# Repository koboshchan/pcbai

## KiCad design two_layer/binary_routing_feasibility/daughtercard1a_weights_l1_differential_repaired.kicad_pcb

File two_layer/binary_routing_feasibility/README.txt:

These four routed binary-model trials are engineering feasibility snapshots only.
They are NOT final grayscale boards and must NOT be fabricated.

DC1a and DC1c have strict zero DRC errors and zero unconnected items.
DC1b and DC1d each have three copper-edge routing errors, zero unconnected items.
Library-footprint warnings remain. No Gerbers or assembly files are released.

Model source was binary trained_circuit.json before approved PWM+RC grayscale
retraining. Final grayscale training and source10050ohm coupled input loading
will change resistor values and connections, requiring regenerated CAD/routers.
Straddle solder-pad tips recessed0.5mm preserve connectorposition and pinpitch;
actual purchased header pinreach still needs mechanical qualification.

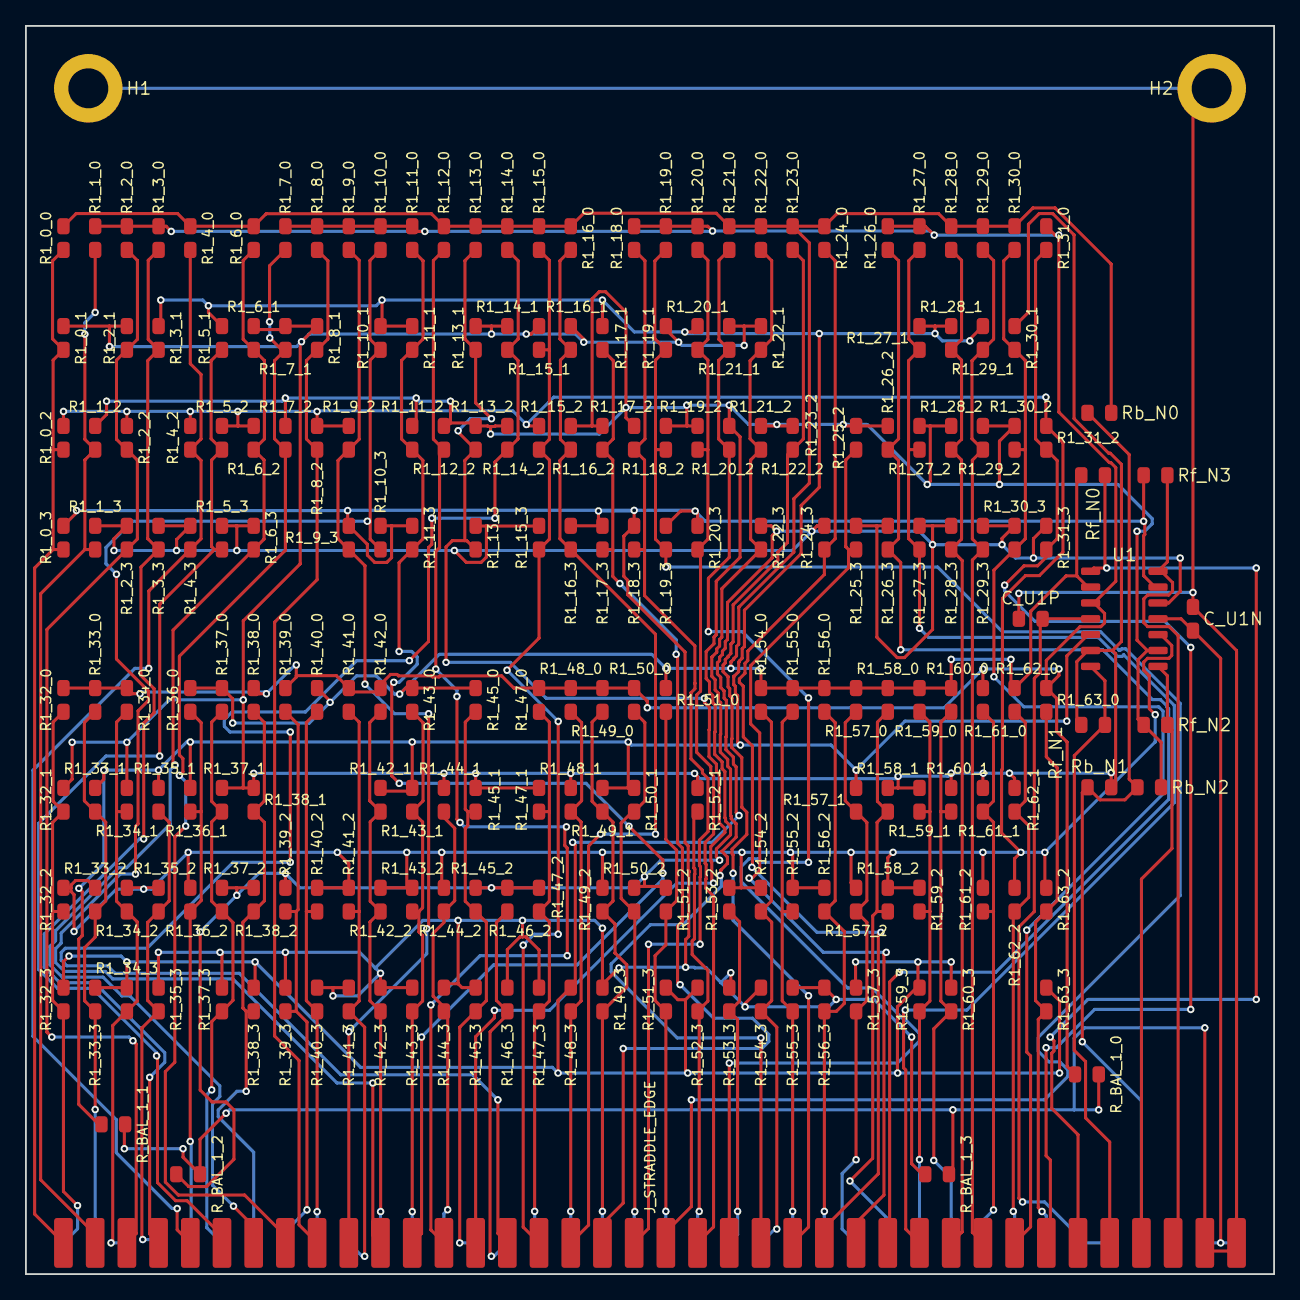
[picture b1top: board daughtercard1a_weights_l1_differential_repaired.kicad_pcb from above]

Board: 2 copper layers, 100.0 x 100.0 mm, 228 parts (0 on the bottom side), 80 nets.

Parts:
C_U1N, C_U1P: 0.1uF; C_0805_2012Metric
H1, H2: MountingHole; MountingHole_3.2mm_M3_Pad
J_STRADDLE_EDGE: PinHeader_2x38_Straddle; PinHeader_2x38_Straddle_P2.54mm
R1_0_0: 36k; R_0805_2012Metric
R1_0_1, R1_7_1, R1_14_2, R1_29_1, R1_31_0, R1_51_3, R1_59_2: 750k; R_0805_2012Metric
R1_0_2, R1_2_2, R1_8_1, R1_21_2, R1_59_0, R1_62_0: 200k; R_0805_2012Metric
R1_0_3, R1_2_3, R1_56_0, R1_62_2: 75k; R_0805_2012Metric
R1_1_0, R1_2_0, R1_8_2, R1_15_0, R1_24_0, R1_25_3, R1_27_0, R1_55_3, R1_59_3: 180k; R_0805_2012Metric
R1_1_2, R1_6_0, R1_21_1, R1_26_0, R1_26_2, R1_35_2, R1_37_1, R1_57_0: 360k; R_0805_2012Metric
R1_1_3, R1_4_3, R1_28_1, R1_31_3, R1_39_0: 91k; R_0805_2012Metric
R1_2_1, R1_11_3, R1_14_0, R1_28_0, R1_29_2, R1_33_0, R1_35_3, R1_38_1, R1_40_0, R1_46_3, R1_49_3, R1_52_3, R1_62_1: 470k; R_0805_2012Metric
R1_3_0, R1_19_0, R1_20_1, R1_22_0, R1_22_1, R1_39_2, R1_41_3, R1_42_2, R1_59_1: 270k; R_0805_2012Metric
R1_3_1, R1_6_1, R1_11_2, R1_34_1, R1_36_1, R1_37_0, R1_38_0, R1_38_2, R1_48_1, R1_53_2, R1_53_3, R1_63_0: 820k; R_0805_2012Metric
R1_3_3, R1_5_2, R1_6_3, R1_48_3: 100k; R_0805_2012Metric
R1_4_0, R1_8_0, R1_23_0, R1_32_0, R1_33_3, R1_56_3, R1_58_1: 240k; R_0805_2012Metric
R1_4_2, R1_9_2, R1_9_3, R1_14_1, R1_18_2, R1_21_0, R1_27_3, R1_37_2, R1_41_0, R1_47_3, R1_58_2: 430k; R_0805_2012Metric
R1_5_1, R1_17_1, R1_43_0, R1_49_0, R1_50_0: 1.6M; R_0805_2012Metric
R1_5_3, R1_57_2: 120k; R_0805_2012Metric
R1_6_2, R1_23_2, R1_55_0: 110k; R_0805_2012Metric
R1_7_0, R1_12_0, R1_27_2, R1_32_1, R1_43_1, R1_54_0, R1_55_2: 510k; R_0805_2012Metric
R1_7_2, R1_15_1, R1_19_2, R1_22_3, R1_25_2, R1_34_0, R1_34_2, R1_36_0, R1_44_2, R1_47_1: 560k; R_0805_2012Metric
R1_9_0, R1_13_0, R1_27_1, R1_29_0, R1_36_2, R1_54_2: 390k; R_0805_2012Metric
R1_10_0, R1_10_3, R1_16_1, R1_44_1, R1_45_1, R1_58_0, R1_60_0: 330k; R_0805_2012Metric
R1_10_1, R1_41_2, R1_42_1, R1_43_3, R1_51_2: 1.3M; R_0805_2012Metric
R1_11_0, R1_12_2, R1_30_0, R1_33_1, R1_61_0: 1.8M; R_0805_2012Metric
R1_11_1, R1_16_2, R1_19_1, R1_28_2, R1_38_3, R1_47_2: 1.5M; R_0805_2012Metric
R1_13_1, R1_20_2, R1_30_1, R1_37_3, R1_45_0, R1_45_2, R1_48_0, R1_49_2: 910k; R_0805_2012Metric
R1_13_2, R1_16_0, R1_17_2, R1_20_0, R1_33_2, R1_34_3, R1_42_3, R1_49_1, R1_52_1: 680k; R_0805_2012Metric
R1_13_3, R1_44_3, R1_45_3, R1_60_1, R1_61_1: 1M; R_0805_2012Metric
R1_15_2, R1_17_3, R1_39_3: 150k; R_0805_2012Metric
R1_15_3: 160k; R_0805_2012Metric
R1_16_3, R1_31_2, R1_61_2: 82k; R_0805_2012Metric
R1_18_0: 3.9M; R_0805_2012Metric
R1_18_3, R1_19_3, R1_35_1, R1_40_2, R1_57_3, R1_60_3: 300k; R_0805_2012Metric
R1_20_3: 3.3M; R_0805_2012Metric
R1_22_2, R1_32_2: 130k; R_0805_2012Metric
R1_24_3, R1_63_3: 51k; R_0805_2012Metric
R1_26_3, R1_43_2, R1_56_2: 220k; R_0805_2012Metric
R1_28_3, R1_29_3, R1_50_1: 1.2M; R_0805_2012Metric
R1_30_2, R1_42_0, R1_57_1: 620k; R_0805_2012Metric
R1_30_3: 2M; R_0805_2012Metric
R1_32_3: 24k; R_0805_2012Metric
R1_40_3, R1_47_0: 68k; R_0805_2012Metric
R1_46_2: 1.1M; R_0805_2012Metric
R1_50_2: 4.3M; R_0805_2012Metric
R1_51_0: 2.2M; R_0805_2012Metric
R1_54_3: 3.6M; R_0805_2012Metric
R1_63_2: 43k; R_0805_2012Metric
R_BAL_1_0: 21.5k; R_0805_2012Metric
R_BAL_1_1: 28.7k; R_0805_2012Metric
R_BAL_1_2: 11.5k; R_0805_2012Metric
R_BAL_1_3: 9.53k; R_0805_2012Metric
Rb_N0: 470k; R_0805_2012Metric
Rb_N1: 910k; R_0805_2012Metric
Rb_N2: 270k; R_0805_2012Metric
Rf_N0, Rf_N1, Rf_N2, Rf_N3: 100k; R_0805_2012Metric
U1: TL074; SOIC-14_3.9x8.7mm_P1.27mm

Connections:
+5V_REF: J_STRADDLE_EDGE.B35, Rb_N0.1, Rb_N1.1, Rb_N2.1
+15V: C_U1P.2, J_STRADDLE_EDGE.B33, J_STRADDLE_EDGE.B34, U1.4
-15V: C_U1N.1, J_STRADDLE_EDGE.B37, J_STRADDLE_EDGE.B38, U1.11
GND: C_U1N.2, C_U1P.1, H1.1, H2.1, J_STRADDLE_EDGE.A37, J_STRADDLE_EDGE.A38, R_BAL_1_0.2, R_BAL_1_1.2, R_BAL_1_2.2, R_BAL_1_3.2
INV_N0: R1_0_0.2, R1_4_0.2, R1_6_0.2, R1_12_0.2, R1_13_0.2, R1_14_0.2, R1_15_0.2, R1_16_0.2, R1_21_0.2, R1_22_0.2, R1_23_0.2, R1_24_0.2, R1_28_0.2, R1_29_0.2, R1_30_0.2, R1_36_0.2, R1_37_0.2, R1_40_0.2, R1_43_0.2, R1_45_0.2, R1_51_0.2, R1_54_0.2, R1_55_0.2, R1_56_0.2, R1_57_0.2, R1_58_0.2, R1_59_0.2, R1_60_0.2, R1_62_0.2, Rb_N0.2, Rf_N0.1, U1.2
INV_N1: R1_0_1.2, R1_2_1.2, R1_6_1.2, R1_7_1.2, R1_8_1.2, R1_13_1.2, R1_14_1.2, R1_15_1.2, R1_16_1.2, R1_19_1.2, R1_21_1.2, R1_22_1.2, R1_30_1.2, R1_32_1.2, R1_34_1.2, R1_37_1.2, R1_38_1.2, R1_44_1.2, R1_45_1.2, R1_47_1.2, R1_48_1.2, R1_52_1.2, R1_58_1.2, R1_59_1.2, R1_60_1.2, R1_61_1.2, R1_62_1.2, Rb_N1.2, Rf_N1.1, U1.6
INV_N2: R1_1_2.2, R1_7_2.2, R1_11_2.2, R1_12_2.2, R1_13_2.2, R1_14_2.2, R1_16_2.2, R1_17_2.2, R1_18_2.2, R1_19_2.2, R1_20_2.2, R1_21_2.2, R1_22_2.2, R1_23_2.2, R1_25_2.2, R1_26_2.2, R1_27_2.2, R1_28_2.2, R1_29_2.2, R1_30_2.2, R1_37_2.2, R1_38_2.2, R1_39_2.2, R1_45_2.2, R1_46_2.2, R1_47_2.2, R1_50_2.2, R1_51_2.2, R_BAL_1_2.1, Rb_N2.2, Rf_N2.1, U1.9
INV_N3: R1_0_3.2, R1_9_3.2, R1_10_3.2, R1_11_3.2, R1_16_3.2, R1_17_3.2, R1_18_3.2, R1_19_3.2, R1_20_3.2, R1_35_3.2, R1_37_3.2, R1_39_3.2, R1_40_3.2, R1_41_3.2, R1_42_3.2, R1_43_3.2, R1_44_3.2, R1_45_3.2, R1_46_3.2, R1_47_3.2, R1_49_3.2, R1_53_3.2, R1_54_3.2, R1_55_3.2, R1_56_3.2, R_BAL_1_3.1, Rf_N3.1, U1.13
IN_0: J_STRADDLE_EDGE.A1, R1_0_0.1, R1_0_1.1, R1_0_2.1, R1_0_3.1
IN_1: J_STRADDLE_EDGE.A2, R1_1_0.1, R1_1_2.1, R1_1_3.1
IN_2: J_STRADDLE_EDGE.A3, R1_2_0.1, R1_2_1.1, R1_2_2.1, R1_2_3.1
IN_3: J_STRADDLE_EDGE.A4, R1_3_0.1, R1_3_1.1, R1_3_3.1
IN_4: J_STRADDLE_EDGE.A5, R1_4_0.1, R1_4_2.1, R1_4_3.1
IN_5: J_STRADDLE_EDGE.A6, R1_5_1.1, R1_5_2.1, R1_5_3.1
IN_6: J_STRADDLE_EDGE.A7, R1_6_0.1, R1_6_1.1, R1_6_2.1, R1_6_3.1
IN_7: J_STRADDLE_EDGE.A8, R1_7_0.1, R1_7_1.1, R1_7_2.1
IN_8: J_STRADDLE_EDGE.A9, R1_8_0.1, R1_8_1.1, R1_8_2.1
IN_9: J_STRADDLE_EDGE.A10, R1_9_0.1, R1_9_2.1, R1_9_3.1
IN_10: J_STRADDLE_EDGE.A11, R1_10_0.1, R1_10_1.1, R1_10_3.1
IN_11: J_STRADDLE_EDGE.A12, R1_11_0.1, R1_11_1.1, R1_11_2.1, R1_11_3.1
IN_12: J_STRADDLE_EDGE.A13, R1_12_0.1, R1_12_2.1
IN_13: J_STRADDLE_EDGE.A14, R1_13_0.1, R1_13_1.1, R1_13_2.1, R1_13_3.1
IN_14: J_STRADDLE_EDGE.A15, R1_14_0.1, R1_14_1.1, R1_14_2.1
IN_15: J_STRADDLE_EDGE.A16, R1_15_0.1, R1_15_1.1, R1_15_2.1, R1_15_3.1
IN_16: J_STRADDLE_EDGE.A17, R1_16_0.1, R1_16_1.1, R1_16_2.1, R1_16_3.1
IN_17: J_STRADDLE_EDGE.A18, R1_17_1.1, R1_17_2.1, R1_17_3.1
IN_18: J_STRADDLE_EDGE.A19, R1_18_0.1, R1_18_2.1, R1_18_3.1
IN_19: J_STRADDLE_EDGE.A20, R1_19_0.1, R1_19_1.1, R1_19_2.1, R1_19_3.1
IN_20: J_STRADDLE_EDGE.A21, R1_20_0.1, R1_20_1.1, R1_20_2.1, R1_20_3.1
IN_21: J_STRADDLE_EDGE.A22, R1_21_0.1, R1_21_1.1, R1_21_2.1
IN_22: J_STRADDLE_EDGE.A23, R1_22_0.1, R1_22_1.1, R1_22_2.1, R1_22_3.1
IN_23: J_STRADDLE_EDGE.A24, R1_23_0.1, R1_23_2.1
IN_24: J_STRADDLE_EDGE.A25, R1_24_0.1, R1_24_3.1
IN_25: J_STRADDLE_EDGE.A26, R1_25_2.1, R1_25_3.1
IN_26: J_STRADDLE_EDGE.A27, R1_26_0.1, R1_26_2.1, R1_26_3.1
IN_27: J_STRADDLE_EDGE.A28, R1_27_0.1, R1_27_1.1, R1_27_2.1, R1_27_3.1
IN_28: J_STRADDLE_EDGE.A29, R1_28_0.1, R1_28_1.1, R1_28_2.1, R1_28_3.1
IN_29: J_STRADDLE_EDGE.A30, R1_29_0.1, R1_29_1.1, R1_29_2.1, R1_29_3.1
IN_30: J_STRADDLE_EDGE.A31, R1_30_0.1, R1_30_1.1, R1_30_2.1, R1_30_3.1
IN_31: J_STRADDLE_EDGE.A32, R1_31_0.1, R1_31_2.1, R1_31_3.1
IN_32: J_STRADDLE_EDGE.B1, R1_32_0.1, R1_32_1.1, R1_32_2.1, R1_32_3.1
IN_33: J_STRADDLE_EDGE.B2, R1_33_0.1, R1_33_1.1, R1_33_2.1, R1_33_3.1
IN_34: J_STRADDLE_EDGE.B3, R1_34_0.1, R1_34_1.1, R1_34_2.1, R1_34_3.1
IN_35: J_STRADDLE_EDGE.B4, R1_35_1.1, R1_35_2.1, R1_35_3.1
IN_36: J_STRADDLE_EDGE.B5, R1_36_0.1, R1_36_1.1, R1_36_2.1
IN_37: J_STRADDLE_EDGE.B6, R1_37_0.1, R1_37_1.1, R1_37_2.1, R1_37_3.1
IN_38: J_STRADDLE_EDGE.B7, R1_38_0.1, R1_38_1.1, R1_38_2.1, R1_38_3.1
IN_39: J_STRADDLE_EDGE.B8, R1_39_0.1, R1_39_2.1, R1_39_3.1
IN_40: J_STRADDLE_EDGE.B9, R1_40_0.1, R1_40_2.1, R1_40_3.1
IN_41: J_STRADDLE_EDGE.B10, R1_41_0.1, R1_41_2.1, R1_41_3.1
IN_42: J_STRADDLE_EDGE.B11, R1_42_0.1, R1_42_1.1, R1_42_2.1, R1_42_3.1
IN_43: J_STRADDLE_EDGE.B12, R1_43_0.1, R1_43_1.1, R1_43_2.1, R1_43_3.1
IN_44: J_STRADDLE_EDGE.B13, R1_44_1.1, R1_44_2.1, R1_44_3.1
IN_45: J_STRADDLE_EDGE.B14, R1_45_0.1, R1_45_1.1, R1_45_2.1, R1_45_3.1
IN_46: J_STRADDLE_EDGE.B15, R1_46_2.1, R1_46_3.1
IN_47: J_STRADDLE_EDGE.B16, R1_47_0.1, R1_47_1.1, R1_47_2.1, R1_47_3.1
IN_48: J_STRADDLE_EDGE.B17, R1_48_0.1, R1_48_1.1, R1_48_3.1
IN_49: J_STRADDLE_EDGE.B18, R1_49_0.1, R1_49_1.1, R1_49_2.1, R1_49_3.1
IN_50: J_STRADDLE_EDGE.B19, R1_50_0.1, R1_50_1.1, R1_50_2.1
IN_51: J_STRADDLE_EDGE.B20, R1_51_0.1, R1_51_2.1, R1_51_3.1
IN_52: J_STRADDLE_EDGE.B21, R1_52_1.1, R1_52_3.1
IN_53: J_STRADDLE_EDGE.B22, R1_53_2.1, R1_53_3.1
IN_54: J_STRADDLE_EDGE.B23, R1_54_0.1, R1_54_2.1, R1_54_3.1
IN_55: J_STRADDLE_EDGE.B24, R1_55_0.1, R1_55_2.1, R1_55_3.1
IN_56: J_STRADDLE_EDGE.B25, R1_56_0.1, R1_56_2.1, R1_56_3.1
IN_57: J_STRADDLE_EDGE.B26, R1_57_0.1, R1_57_1.1, R1_57_2.1, R1_57_3.1
IN_58: J_STRADDLE_EDGE.B27, R1_58_0.1, R1_58_1.1, R1_58_2.1
IN_59: J_STRADDLE_EDGE.B28, R1_59_0.1, R1_59_1.1, R1_59_2.1, R1_59_3.1
IN_60: J_STRADDLE_EDGE.B29, R1_60_0.1, R1_60_1.1, R1_60_3.1
IN_61: J_STRADDLE_EDGE.B30, R1_61_0.1, R1_61_1.1, R1_61_2.1
IN_62: J_STRADDLE_EDGE.B31, R1_62_0.1, R1_62_1.1, R1_62_2.1
IN_63: J_STRADDLE_EDGE.B32, R1_63_0.1, R1_63_2.1, R1_63_3.1
POS_N0: R1_1_0.2, R1_2_0.2, R1_3_0.2, R1_7_0.2, R1_8_0.2, R1_9_0.2, R1_10_0.2, R1_11_0.2, R1_18_0.2, R1_19_0.2, R1_20_0.2, R1_26_0.2, R1_27_0.2, R1_31_0.2, R1_32_0.2, R1_33_0.2, R1_34_0.2, R1_38_0.2, R1_39_0.2, R1_41_0.2, R1_42_0.2, R1_47_0.2, R1_48_0.2, R1_49_0.2, R1_50_0.2, R1_61_0.2, R1_63_0.2, R_BAL_1_0.1, U1.3
POS_N1: R1_3_1.2, R1_5_1.2, R1_10_1.2, R1_11_1.2, R1_17_1.2, R1_20_1.2, R1_27_1.2, R1_28_1.2, R1_29_1.2, R1_33_1.2, R1_35_1.2, R1_36_1.2, R1_42_1.2, R1_43_1.2, R1_49_1.2, R1_50_1.2, R1_57_1.2, R_BAL_1_1.1, U1.5
POS_N2: R1_0_2.2, R1_2_2.2, R1_4_2.2, R1_5_2.2, R1_6_2.2, R1_8_2.2, R1_9_2.2, R1_15_2.2, R1_31_2.2, R1_32_2.2, R1_33_2.2, R1_34_2.2, R1_35_2.2, R1_36_2.2, R1_40_2.2, R1_41_2.2, R1_42_2.2, R1_43_2.2, R1_44_2.2, R1_49_2.2, R1_53_2.2, R1_54_2.2, R1_55_2.2, R1_56_2.2, R1_57_2.2, R1_58_2.2, R1_59_2.2, R1_61_2.2, R1_62_2.2, R1_63_2.2, U1.10
POS_N3: R1_1_3.2, R1_2_3.2, R1_3_3.2, R1_4_3.2, R1_5_3.2, R1_6_3.2, R1_13_3.2, R1_15_3.2, R1_22_3.2, R1_24_3.2, R1_25_3.2, R1_26_3.2, R1_27_3.2, R1_28_3.2, R1_29_3.2, R1_30_3.2, R1_31_3.2, R1_32_3.2, R1_33_3.2, R1_34_3.2, R1_38_3.2, R1_48_3.2, R1_51_3.2, R1_52_3.2, R1_57_3.2, R1_59_3.2, R1_60_3.2, R1_63_3.2, U1.12
V_SUM_0: J_STRADDLE_EDGE.A33, Rf_N0.2, U1.1
V_SUM_1: J_STRADDLE_EDGE.A34, Rf_N1.2, U1.7
V_SUM_2: J_STRADDLE_EDGE.A35, Rf_N2.2, U1.8
V_SUM_3: J_STRADDLE_EDGE.A36, Rf_N3.2, U1.14

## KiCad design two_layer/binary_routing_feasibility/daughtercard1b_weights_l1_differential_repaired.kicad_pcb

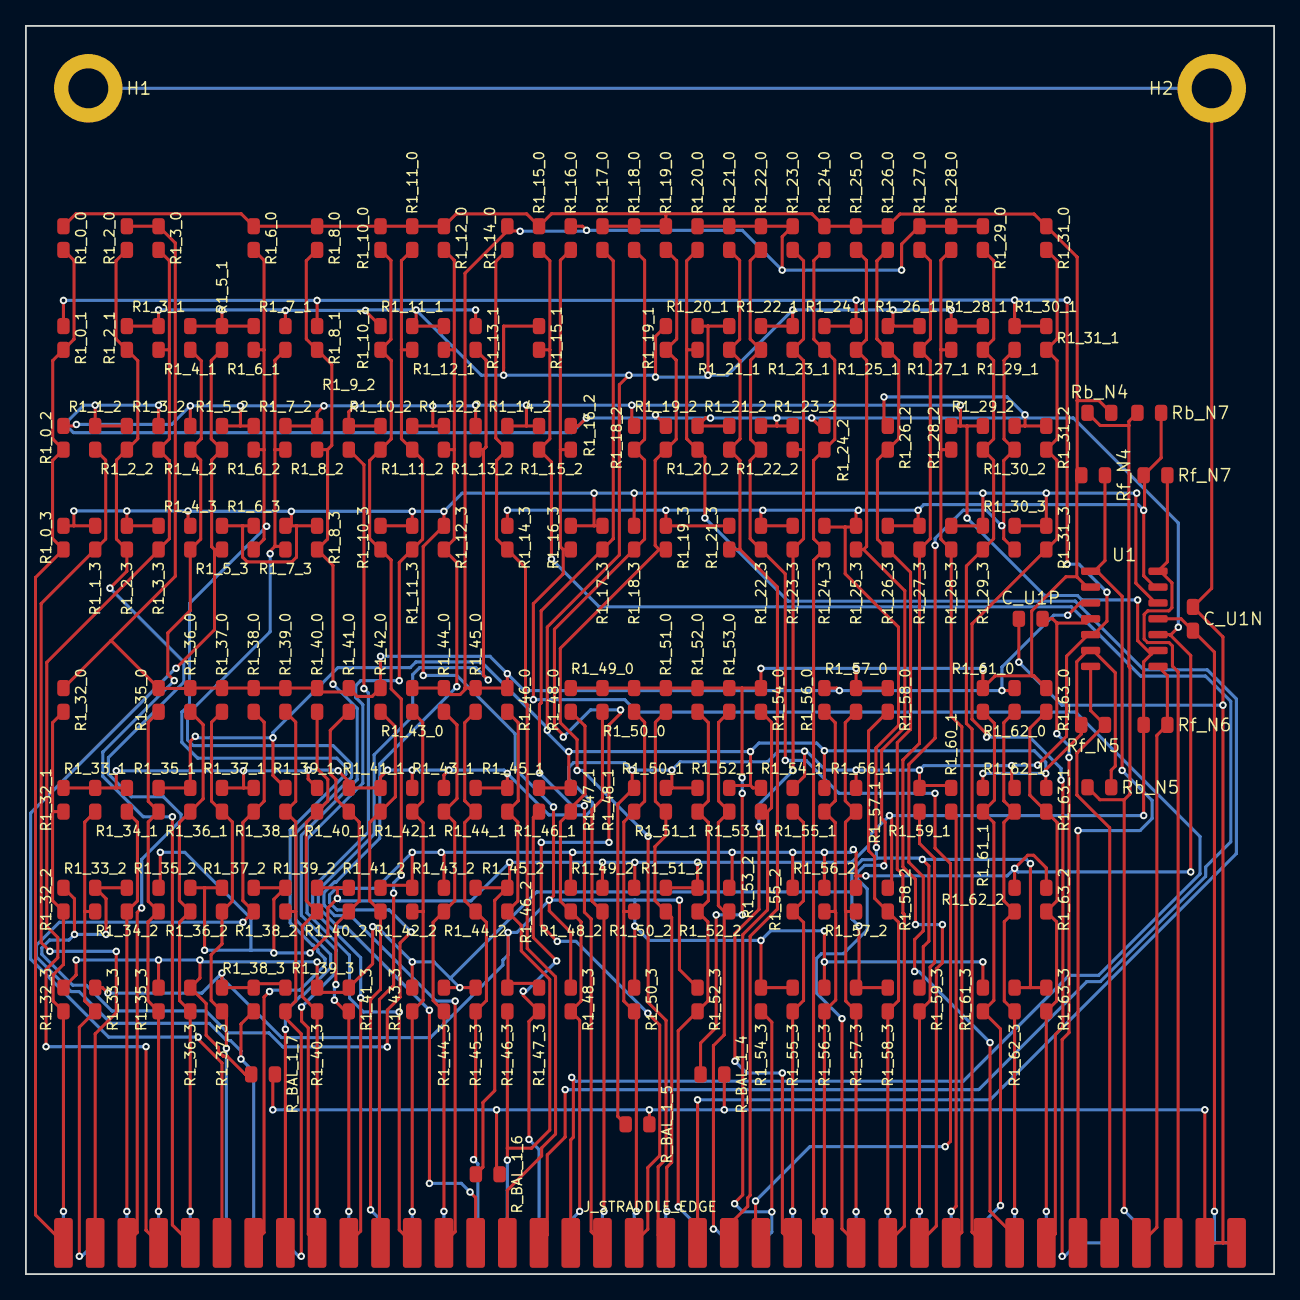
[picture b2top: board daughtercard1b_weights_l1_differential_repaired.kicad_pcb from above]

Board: 2 copper layers, 100.0 x 100.0 mm, 234 parts (0 on the bottom side), 80 nets.

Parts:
C_U1N, C_U1P: 0.1uF; C_0805_2012Metric
H1, H2: MountingHole; MountingHole_3.2mm_M3_Pad
J_STRADDLE_EDGE: PinHeader_2x38_Straddle; PinHeader_2x38_Straddle_P2.54mm
R1_0_0, R1_4_3, R1_16_2, R1_38_3, R1_55_3: 100k; R_0805_2012Metric
R1_0_1, R1_15_2, R1_56_1, R1_56_2: 56k; R_0805_2012Metric
R1_0_2, R1_3_2, R1_6_0, R1_10_1, R1_22_0, R1_28_0, R1_28_3, R1_35_0, R1_37_2, R1_38_2: 330k; R_0805_2012Metric
R1_0_3, R1_7_1, R1_32_0: 51k; R_0805_2012Metric
R1_1_2, R1_2_3, R1_20_0, R1_24_0, R1_27_0, R1_28_1, R1_55_1: 300k; R_0805_2012Metric
R1_1_3, R1_39_0, R1_62_2: 75k; R_0805_2012Metric
R1_2_0, R1_2_2, R1_3_1, R1_4_2, R1_11_0, R1_22_3, R1_43_0, R1_46_2, R1_52_0, R1_58_0, R1_61_3: 270k; R_0805_2012Metric
R1_2_1, R1_17_0, R1_21_1, R1_35_3, R1_43_3, R1_52_2, R1_62_3: 680k; R_0805_2012Metric
R1_3_0, R1_5_2, R1_16_0, R1_16_3, R1_31_0, R1_32_2, R1_39_2, R1_49_0, R1_56_0, R1_63_2: 150k; R_0805_2012Metric
R1_3_3, R1_27_1, R1_42_1, R1_47_1, R1_54_0, R1_55_2, R1_57_2, R1_62_1, R1_63_0: 220k; R_0805_2012Metric
R1_4_1, R1_12_0, R1_14_0, R1_14_3, R1_36_2, R1_41_3, R1_44_0, R1_50_1, R1_51_1: 620k; R_0805_2012Metric
R1_5_1, R1_9_2, R1_57_1: 560k; R_0805_2012Metric
R1_5_3, R1_32_1, R1_40_1, R1_47_3: 91k; R_0805_2012Metric
R1_6_1, R1_52_1: 1.3M; R_0805_2012Metric
R1_6_2, R1_7_2, R1_41_0: 82k; R_0805_2012Metric
R1_6_3: 68k; R_0805_2012Metric
R1_7_3, R1_23_1, R1_48_2: 120k; R_0805_2012Metric
R1_8_0, R1_15_0, R1_37_1, R1_44_2, R1_52_3: 2.4M; R_0805_2012Metric
R1_8_1, R1_20_2, R1_24_3, R1_32_3: 200k; R_0805_2012Metric
R1_8_2: 5.6M; R_0805_2012Metric
R1_8_3, R1_21_2, R1_22_2, R1_31_1: 110k; R_0805_2012Metric
R1_10_0, R1_24_2, R1_30_2, R1_48_0: 470k; R_0805_2012Metric
R1_10_2, R1_11_2, R1_18_2, R1_50_3: 1.5M; R_0805_2012Metric
R1_10_3, R1_12_3, R1_19_3, R1_21_3, R1_38_1, R1_49_2: 2M; R_0805_2012Metric
R1_11_1, R1_18_0, R1_25_0, R1_29_0, R1_33_1, R1_35_1, R1_61_0: 430k; R_0805_2012Metric
R1_11_3, R1_19_0, R1_42_2, R1_51_2, R1_60_1: 910k; R_0805_2012Metric
R1_12_1, R1_34_1, R1_34_2, R1_36_1, R1_37_3, R1_48_1, R1_53_1: 1.2M; R_0805_2012Metric
R1_12_2, R1_20_1, R1_22_1, R1_29_2, R1_45_1, R1_57_0, R1_59_1: 820k; R_0805_2012Metric
R1_13_1, R1_19_1, R1_29_1, R1_35_2: 1.8M; R_0805_2012Metric
R1_13_2, R1_33_2, R1_37_0, R1_43_1, R1_45_2, R1_51_0, R1_63_1: 390k; R_0805_2012Metric
R1_14_2, R1_38_0, R1_40_3, R1_46_3, R1_53_0: 180k; R_0805_2012Metric
R1_15_1, R1_41_1, R1_50_0, R1_54_3, R1_58_2: 240k; R_0805_2012Metric
R1_17_3: 3M; R_0805_2012Metric
R1_18_3, R1_46_1: 4.3M; R_0805_2012Metric
R1_19_2, R1_25_1, R1_46_0, R1_48_3, R1_50_2, R1_61_1: 1.1M; R_0805_2012Metric
R1_21_0, R1_28_2, R1_43_2, R1_44_3, R1_56_3: 510k; R_0805_2012Metric
R1_23_0, R1_24_1: 130k; R_0805_2012Metric
R1_23_2, R1_31_2, R1_31_3: 39k; R_0805_2012Metric
R1_23_3: 30k; R_0805_2012Metric
R1_25_3, R1_26_0, R1_33_3, R1_39_1, R1_44_1, R1_45_0: 750k; R_0805_2012Metric
R1_26_1, R1_45_3, R1_54_1: 1M; R_0805_2012Metric
R1_26_2, R1_26_3, R1_27_3, R1_41_2, R1_53_2, R1_57_3: 2.2M; R_0805_2012Metric
R1_29_3: 62k; R_0805_2012Metric
R1_30_1: 3.3M; R_0805_2012Metric
R1_30_3: 22k; R_0805_2012Metric
R1_36_0, R1_40_2: 360k; R_0805_2012Metric
R1_36_3: 2.7M; R_0805_2012Metric
R1_39_3: 27k; R_0805_2012Metric
R1_40_0: 43k; R_0805_2012Metric
R1_42_0, R1_62_0: 160k; R_0805_2012Metric
R1_58_3, R1_59_3: 1.6M; R_0805_2012Metric
R1_63_3: 47k; R_0805_2012Metric
R_BAL_1_4: 16.9k; R_0805_2012Metric
R_BAL_1_5: 80.6k; R_0805_2012Metric
R_BAL_1_6: 18.2k; R_0805_2012Metric
R_BAL_1_7: 5.62k; R_0805_2012Metric
Rb_N4: 330k; R_0805_2012Metric
Rb_N5: 240k; R_0805_2012Metric
Rb_N7: 360k; R_0805_2012Metric
Rf_N4, Rf_N5, Rf_N6, Rf_N7: 100k; R_0805_2012Metric
U1: TL074; SOIC-14_3.9x8.7mm_P1.27mm

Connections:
+5V_REF: J_STRADDLE_EDGE.B35, Rb_N4.1, Rb_N5.1, Rb_N7.1
+15V: C_U1P.2, J_STRADDLE_EDGE.B33, J_STRADDLE_EDGE.B34, U1.4
-15V: C_U1N.1, J_STRADDLE_EDGE.B37, J_STRADDLE_EDGE.B38, U1.11
GND: C_U1N.2, C_U1P.1, H1.1, H2.1, J_STRADDLE_EDGE.A37, J_STRADDLE_EDGE.A38, R_BAL_1_4.2, R_BAL_1_5.2, R_BAL_1_6.2, R_BAL_1_7.2
INV_N4: R1_0_0.2, R1_6_0.2, R1_8_0.2, R1_10_0.2, R1_11_0.2, R1_12_0.2, R1_15_0.2, R1_17_0.2, R1_18_0.2, R1_19_0.2, R1_24_0.2, R1_25_0.2, R1_26_0.2, R1_31_0.2, R1_48_0.2, R1_49_0.2, R1_50_0.2, R1_51_0.2, R1_52_0.2, R1_53_0.2, R1_54_0.2, R1_57_0.2, R1_58_0.2, R1_61_0.2, R1_63_0.2, R_BAL_1_4.1, Rb_N4.2, Rf_N4.1, U1.2
INV_N5: R1_2_1.2, R1_3_1.2, R1_4_1.2, R1_5_1.2, R1_6_1.2, R1_7_1.2, R1_10_1.2, R1_11_1.2, R1_12_1.2, R1_13_1.2, R1_15_1.2, R1_19_1.2, R1_20_1.2, R1_21_1.2, R1_22_1.2, R1_23_1.2, R1_26_1.2, R1_27_1.2, R1_28_1.2, R1_29_1.2, R1_35_1.2, R1_36_1.2, R1_39_1.2, R1_47_1.2, R1_48_1.2, R1_53_1.2, R1_54_1.2, R1_56_1.2, R1_61_1.2, R1_63_1.2, Rb_N5.2, Rf_N5.1, U1.6
INV_N6: R1_0_2.2, R1_4_2.2, R1_5_2.2, R1_6_2.2, R1_7_2.2, R1_8_2.2, R1_9_2.2, R1_10_2.2, R1_11_2.2, R1_12_2.2, R1_13_2.2, R1_14_2.2, R1_15_2.2, R1_18_2.2, R1_28_2.2, R1_29_2.2, R1_35_2.2, R1_36_2.2, R1_37_2.2, R1_38_2.2, R1_39_2.2, R1_40_2.2, R1_41_2.2, R1_45_2.2, R1_46_2.2, R1_49_2.2, R1_50_2.2, R1_51_2.2, R1_52_2.2, R1_58_2.2, R_BAL_1_6.1, Rf_N6.1, U1.9
INV_N7: R1_14_3.2, R1_19_3.2, R1_21_3.2, R1_22_3.2, R1_23_3.2, R1_24_3.2, R1_25_3.2, R1_26_3.2, R1_27_3.2, R1_32_3.2, R1_35_3.2, R1_36_3.2, R1_40_3.2, R1_41_3.2, R1_43_3.2, R1_44_3.2, R1_45_3.2, R1_57_3.2, R1_58_3.2, R1_59_3.2, R1_62_3.2, R1_63_3.2, R_BAL_1_7.1, Rb_N7.2, Rf_N7.1, U1.13
IN_0: J_STRADDLE_EDGE.A1, R1_0_0.1, R1_0_1.1, R1_0_2.1, R1_0_3.1
IN_1: J_STRADDLE_EDGE.A2, R1_1_2.1, R1_1_3.1
IN_2: J_STRADDLE_EDGE.A3, R1_2_0.1, R1_2_1.1, R1_2_2.1, R1_2_3.1
IN_3: J_STRADDLE_EDGE.A4, R1_3_0.1, R1_3_1.1, R1_3_2.1, R1_3_3.1
IN_4: J_STRADDLE_EDGE.A5, R1_4_1.1, R1_4_2.1, R1_4_3.1
IN_5: J_STRADDLE_EDGE.A6, R1_5_1.1, R1_5_2.1, R1_5_3.1
IN_6: J_STRADDLE_EDGE.A7, R1_6_0.1, R1_6_1.1, R1_6_2.1, R1_6_3.1
IN_7: J_STRADDLE_EDGE.A8, R1_7_1.1, R1_7_2.1, R1_7_3.1
IN_8: J_STRADDLE_EDGE.A9, R1_8_0.1, R1_8_1.1, R1_8_2.1, R1_8_3.1
IN_9: J_STRADDLE_EDGE.A10, R1_9_2.1
IN_10: J_STRADDLE_EDGE.A11, R1_10_0.1, R1_10_1.1, R1_10_2.1, R1_10_3.1
IN_11: J_STRADDLE_EDGE.A12, R1_11_0.1, R1_11_1.1, R1_11_2.1, R1_11_3.1
IN_12: J_STRADDLE_EDGE.A13, R1_12_0.1, R1_12_1.1, R1_12_2.1, R1_12_3.1
IN_13: J_STRADDLE_EDGE.A14, R1_13_1.1, R1_13_2.1
IN_14: J_STRADDLE_EDGE.A15, R1_14_0.1, R1_14_2.1, R1_14_3.1
IN_15: J_STRADDLE_EDGE.A16, R1_15_0.1, R1_15_1.1, R1_15_2.1
IN_16: J_STRADDLE_EDGE.A17, R1_16_0.1, R1_16_2.1, R1_16_3.1
IN_17: J_STRADDLE_EDGE.A18, R1_17_0.1, R1_17_3.1
IN_18: J_STRADDLE_EDGE.A19, R1_18_0.1, R1_18_2.1, R1_18_3.1
IN_19: J_STRADDLE_EDGE.A20, R1_19_0.1, R1_19_1.1, R1_19_2.1, R1_19_3.1
IN_20: J_STRADDLE_EDGE.A21, R1_20_0.1, R1_20_1.1, R1_20_2.1
IN_21: J_STRADDLE_EDGE.A22, R1_21_0.1, R1_21_1.1, R1_21_2.1, R1_21_3.1
IN_22: J_STRADDLE_EDGE.A23, R1_22_0.1, R1_22_1.1, R1_22_2.1, R1_22_3.1
IN_23: J_STRADDLE_EDGE.A24, R1_23_0.1, R1_23_1.1, R1_23_2.1, R1_23_3.1
IN_24: J_STRADDLE_EDGE.A25, R1_24_0.1, R1_24_1.1, R1_24_2.1, R1_24_3.1
IN_25: J_STRADDLE_EDGE.A26, R1_25_0.1, R1_25_1.1, R1_25_3.1
IN_26: J_STRADDLE_EDGE.A27, R1_26_0.1, R1_26_1.1, R1_26_2.1, R1_26_3.1
IN_27: J_STRADDLE_EDGE.A28, R1_27_0.1, R1_27_1.1, R1_27_3.1
IN_28: J_STRADDLE_EDGE.A29, R1_28_0.1, R1_28_1.1, R1_28_2.1, R1_28_3.1
IN_29: J_STRADDLE_EDGE.A30, R1_29_0.1, R1_29_1.1, R1_29_2.1, R1_29_3.1
IN_30: J_STRADDLE_EDGE.A31, R1_30_1.1, R1_30_2.1, R1_30_3.1
IN_31: J_STRADDLE_EDGE.A32, R1_31_0.1, R1_31_1.1, R1_31_2.1, R1_31_3.1
IN_32: J_STRADDLE_EDGE.B1, R1_32_0.1, R1_32_1.1, R1_32_2.1, R1_32_3.1
IN_33: J_STRADDLE_EDGE.B2, R1_33_1.1, R1_33_2.1, R1_33_3.1
IN_34: J_STRADDLE_EDGE.B3, R1_34_1.1, R1_34_2.1
IN_35: J_STRADDLE_EDGE.B4, R1_35_0.1, R1_35_1.1, R1_35_2.1, R1_35_3.1
IN_36: J_STRADDLE_EDGE.B5, R1_36_0.1, R1_36_1.1, R1_36_2.1, R1_36_3.1
IN_37: J_STRADDLE_EDGE.B6, R1_37_0.1, R1_37_1.1, R1_37_2.1, R1_37_3.1
IN_38: J_STRADDLE_EDGE.B7, R1_38_0.1, R1_38_1.1, R1_38_2.1, R1_38_3.1
IN_39: J_STRADDLE_EDGE.B8, R1_39_0.1, R1_39_1.1, R1_39_2.1, R1_39_3.1
IN_40: J_STRADDLE_EDGE.B9, R1_40_0.1, R1_40_1.1, R1_40_2.1, R1_40_3.1
IN_41: J_STRADDLE_EDGE.B10, R1_41_0.1, R1_41_1.1, R1_41_2.1, R1_41_3.1
IN_42: J_STRADDLE_EDGE.B11, R1_42_0.1, R1_42_1.1, R1_42_2.1
IN_43: J_STRADDLE_EDGE.B12, R1_43_0.1, R1_43_1.1, R1_43_2.1, R1_43_3.1
IN_44: J_STRADDLE_EDGE.B13, R1_44_0.1, R1_44_1.1, R1_44_2.1, R1_44_3.1
IN_45: J_STRADDLE_EDGE.B14, R1_45_0.1, R1_45_1.1, R1_45_2.1, R1_45_3.1
IN_46: J_STRADDLE_EDGE.B15, R1_46_0.1, R1_46_1.1, R1_46_2.1, R1_46_3.1
IN_47: J_STRADDLE_EDGE.B16, R1_47_1.1, R1_47_3.1
IN_48: J_STRADDLE_EDGE.B17, R1_48_0.1, R1_48_1.1, R1_48_2.1, R1_48_3.1
IN_49: J_STRADDLE_EDGE.B18, R1_49_0.1, R1_49_2.1
IN_50: J_STRADDLE_EDGE.B19, R1_50_0.1, R1_50_1.1, R1_50_2.1, R1_50_3.1
IN_51: J_STRADDLE_EDGE.B20, R1_51_0.1, R1_51_1.1, R1_51_2.1
IN_52: J_STRADDLE_EDGE.B21, R1_52_0.1, R1_52_1.1, R1_52_2.1, R1_52_3.1
IN_53: J_STRADDLE_EDGE.B22, R1_53_0.1, R1_53_1.1, R1_53_2.1
IN_54: J_STRADDLE_EDGE.B23, R1_54_0.1, R1_54_1.1, R1_54_3.1
IN_55: J_STRADDLE_EDGE.B24, R1_55_1.1, R1_55_2.1, R1_55_3.1
IN_56: J_STRADDLE_EDGE.B25, R1_56_0.1, R1_56_1.1, R1_56_2.1, R1_56_3.1
IN_57: J_STRADDLE_EDGE.B26, R1_57_0.1, R1_57_1.1, R1_57_2.1, R1_57_3.1
IN_58: J_STRADDLE_EDGE.B27, R1_58_0.1, R1_58_2.1, R1_58_3.1
IN_59: J_STRADDLE_EDGE.B28, R1_59_1.1, R1_59_3.1
IN_60: J_STRADDLE_EDGE.B29, R1_60_1.1
IN_61: J_STRADDLE_EDGE.B30, R1_61_0.1, R1_61_1.1, R1_61_3.1
IN_62: J_STRADDLE_EDGE.B31, R1_62_0.1, R1_62_1.1, R1_62_2.1, R1_62_3.1
IN_63: J_STRADDLE_EDGE.B32, R1_63_0.1, R1_63_1.1, R1_63_2.1, R1_63_3.1
POS_N4: R1_2_0.2, R1_3_0.2, R1_14_0.2, R1_16_0.2, R1_20_0.2, R1_21_0.2, R1_22_0.2, R1_23_0.2, R1_27_0.2, R1_28_0.2, R1_29_0.2, R1_32_0.2, R1_35_0.2, R1_36_0.2, R1_37_0.2, R1_38_0.2, R1_39_0.2, R1_40_0.2, R1_41_0.2, R1_42_0.2, R1_43_0.2, R1_44_0.2, R1_45_0.2, R1_46_0.2, R1_56_0.2, R1_62_0.2, U1.3
POS_N5: R1_0_1.2, R1_8_1.2, R1_24_1.2, R1_25_1.2, R1_30_1.2, R1_31_1.2, R1_32_1.2, R1_33_1.2, R1_34_1.2, R1_37_1.2, R1_38_1.2, R1_40_1.2, R1_41_1.2, R1_42_1.2, R1_43_1.2, R1_44_1.2, R1_45_1.2, R1_46_1.2, R1_50_1.2, R1_51_1.2, R1_52_1.2, R1_55_1.2, R1_57_1.2, R1_59_1.2, R1_60_1.2, R1_62_1.2, R_BAL_1_5.1, U1.5
POS_N6: R1_1_2.2, R1_2_2.2, R1_3_2.2, R1_16_2.2, R1_19_2.2, R1_20_2.2, R1_21_2.2, R1_22_2.2, R1_23_2.2, R1_24_2.2, R1_26_2.2, R1_30_2.2, R1_31_2.2, R1_32_2.2, R1_33_2.2, R1_34_2.2, R1_42_2.2, R1_43_2.2, R1_44_2.2, R1_48_2.2, R1_53_2.2, R1_55_2.2, R1_56_2.2, R1_57_2.2, R1_62_2.2, R1_63_2.2, U1.10
POS_N7: R1_0_3.2, R1_1_3.2, R1_2_3.2, R1_3_3.2, R1_4_3.2, R1_5_3.2, R1_6_3.2, R1_7_3.2, R1_8_3.2, R1_10_3.2, R1_11_3.2, R1_12_3.2, R1_16_3.2, R1_17_3.2, R1_18_3.2, R1_28_3.2, R1_29_3.2, R1_30_3.2, R1_31_3.2, R1_33_3.2, R1_37_3.2, R1_38_3.2, R1_39_3.2, R1_46_3.2, R1_47_3.2, R1_48_3.2, R1_50_3.2, R1_52_3.2, R1_54_3.2, R1_55_3.2, R1_56_3.2, R1_61_3.2, U1.12
V_SUM_4: J_STRADDLE_EDGE.A33, Rf_N4.2, U1.1
V_SUM_5: J_STRADDLE_EDGE.A34, Rf_N5.2, U1.7
V_SUM_6: J_STRADDLE_EDGE.A35, Rf_N6.2, U1.8
V_SUM_7: J_STRADDLE_EDGE.A36, Rf_N7.2, U1.14
